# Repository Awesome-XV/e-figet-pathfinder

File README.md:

# e-figet-pathfinder
This is a project that allows you to play around with switches and LED's. It's a reaction game ... for now, I am planning to make a settings/page button that allows you to play different game modes and stuff. But now it's geared toward an *F1* style gameplay where the LED's close in on the center light and then they all go blank and it measures the time for you to let go of the "clutch" and hit the "accelerator". Maybe different racing types later??
I made this project as an intro into PCB's, circuits and soldering because it's my first physical project that I have done. I wanted to get into the hardware project and there was a nice guide, but no soldering guide so I get to do that on my own. So this is a bit later, and I added a battery compartment to it, it's now a mobile device and it doesn't have to be plugged in. I also am now planning to add a GT practice shifter to the code where you can practice shifting GT style. I also had to add 2 connectors so that I can solder the battery wires correctly.

# Some Pics

# BOM Table
| Name | Purpose | Quantity | Total Cost (USD) | Distributor | Link |
|------|---------|:--------:|-----------------:|-------------|------|
| XIAO RP2040 | MC, controls everything | 1 | $4.68 | Digikey | [Buy](https://www.digikey.com/en/products/detail/seeed-technology-co-ltd/102010428/14672129) |
| LED RED 5MM | Lights up | 7 | $1.05 | Digikey | [Buy](https://www.digikey.com/en/products/detail/w%C3%BCrth-elektronik/151051RS11000/4490012) |
| Through Hole Resistors | For the LEDs | 10 | $0.22 | Digikey | [Buy](https://www.digikey.com/en/products/detail/stackpole-electronics-inc/CF18JT110R/1741570) |
| MX SWITCH 12V | Switch to trigger actions | 4 | $5.00 | Digikey | [Buy](https://www.digikey.com/en/products/detail/cherry-americas-llc/MX1A-C1NW/280855) |
| BLACK KEYCAPS | Keycaps for the MX switches | 1 | $5.95 | Digikey | [Buy](https://www.digikey.com/en/products/detail/adafruit-industries-llc/4997/14552180) |
| Battery Compartment | To hold the batteries | 1 | $1.77 | Digikey | [Buy](https://www.digikey.com/en/products/detail/keystone-electronics/2465/303814) |
| Connectors | To provide a place for the red and black wires to hook onto | 10 | $0.29 | Digikey | [Buy](https://www.digikey.com/en/products/detail/adam-tech/PH1-01-UA/9830231) |
| Diode | To prevent reverse current flow | 1 | $0.18 | Digikey | [Buy](https://www.digikey.com/en/products/detail/smc-diode-solutions/1N5817/21705460) |
| PCB | For connection | 1 | $2.00 | JLCPCB | N/A |
| Shipping | Move these parts | 1 | $10.29 | JLCPCB, Digikey | N/A |
| Tax | I have to pay | 1 | $2.22 | Digikey | N/A |
| Tariffs | Quantity means 5 products I have tax on | 5 | $0.79 | Digikey | N/A |
| **Total** | | | *$34.44* | | |

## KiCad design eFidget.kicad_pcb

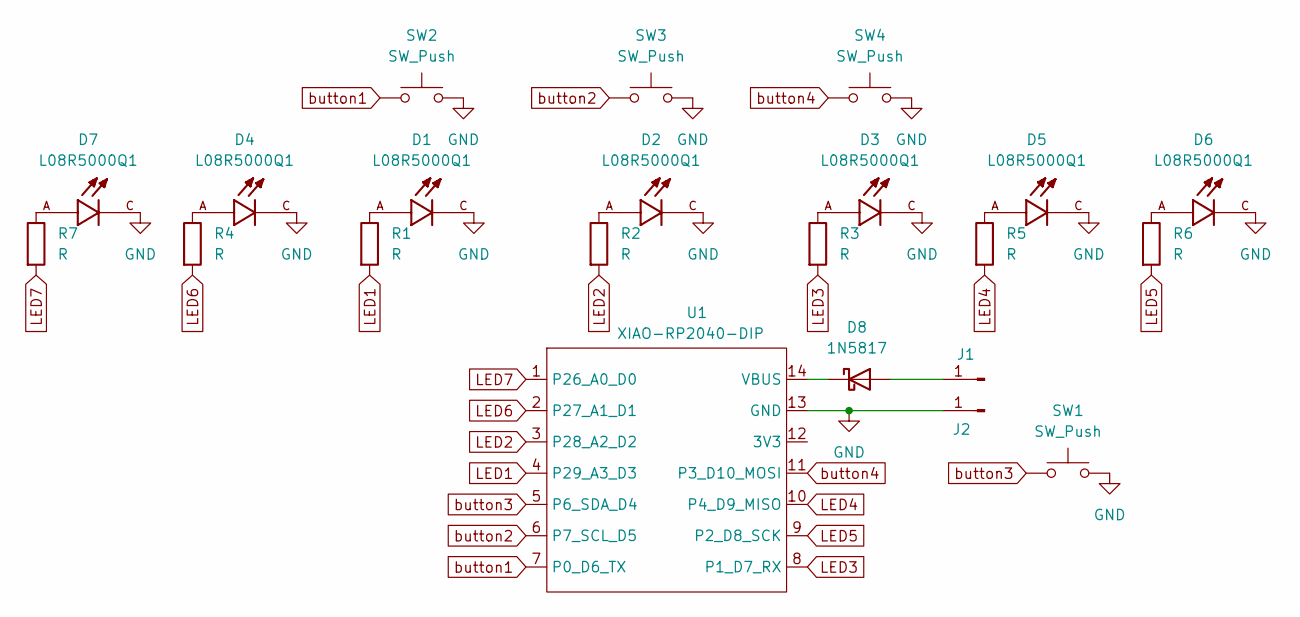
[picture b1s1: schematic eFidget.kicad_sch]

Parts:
D1, D2, D3, D4, D5, D6, D7: L08R5000Q1; LEDRD254W57D500H1070; PARTREV NA
D8: 1N5817; D_DO-41_SOD81_P10.16mm_Horizontal
J1, J2: Conn_01x01_Pin; PinHeader_1x01_P2.54mm_Vertical
R1, R2, R3, R4, R5, R6, R7: R; R_Axial_DIN0204_L3.6mm_D1.6mm_P5.08mm_Horizontal
SW1, SW2, SW3, SW4: SW_Push; SW_Cherry_MX_1.00u_PCB
U1: XIAO-RP2040-DIP

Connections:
GND: D1.C, D2.C, D3.C, D4.C, D5.C, D6.C, D7.C, J2.1, SW1.2, SW2.2, SW3.2, SW4.2, U1.13 (GND)
LED1: R1.2, U1.4 (P29_A3_D3)
LED2: R2.2, U1.3 (P28_A2_D2)
LED3: R3.2, U1.8 (P1_D7_RX)
LED4: R5.2, U1.10 (P4_D9_MISO)
LED5: R6.2, U1.9 (P2_D8_SCK)
LED6: R4.2, U1.2 (P27_A1_D1)
LED7: R7.2, U1.1 (P26_A0_D0)
unnamed: D1.A, R1.1
unnamed: D2.A, R2.1
unnamed: D3.A, R3.1
unnamed: D4.A, R4.1
unnamed: D5.A, R5.1
unnamed: D6.A, R6.1
unnamed: D7.A, R7.1
unnamed: D8.2 (A), J1.1
unnamed: D8.1 (K), U1.14 (VBUS)
button1: SW2.1, U1.7 (P0_D6_TX)
button2: SW3.1, U1.6 (P7_SCL_D5)
button3: SW1.1, U1.5 (P6_SDA_D4)
button4: SW4.1, U1.11 (P3_D10_MOSI)

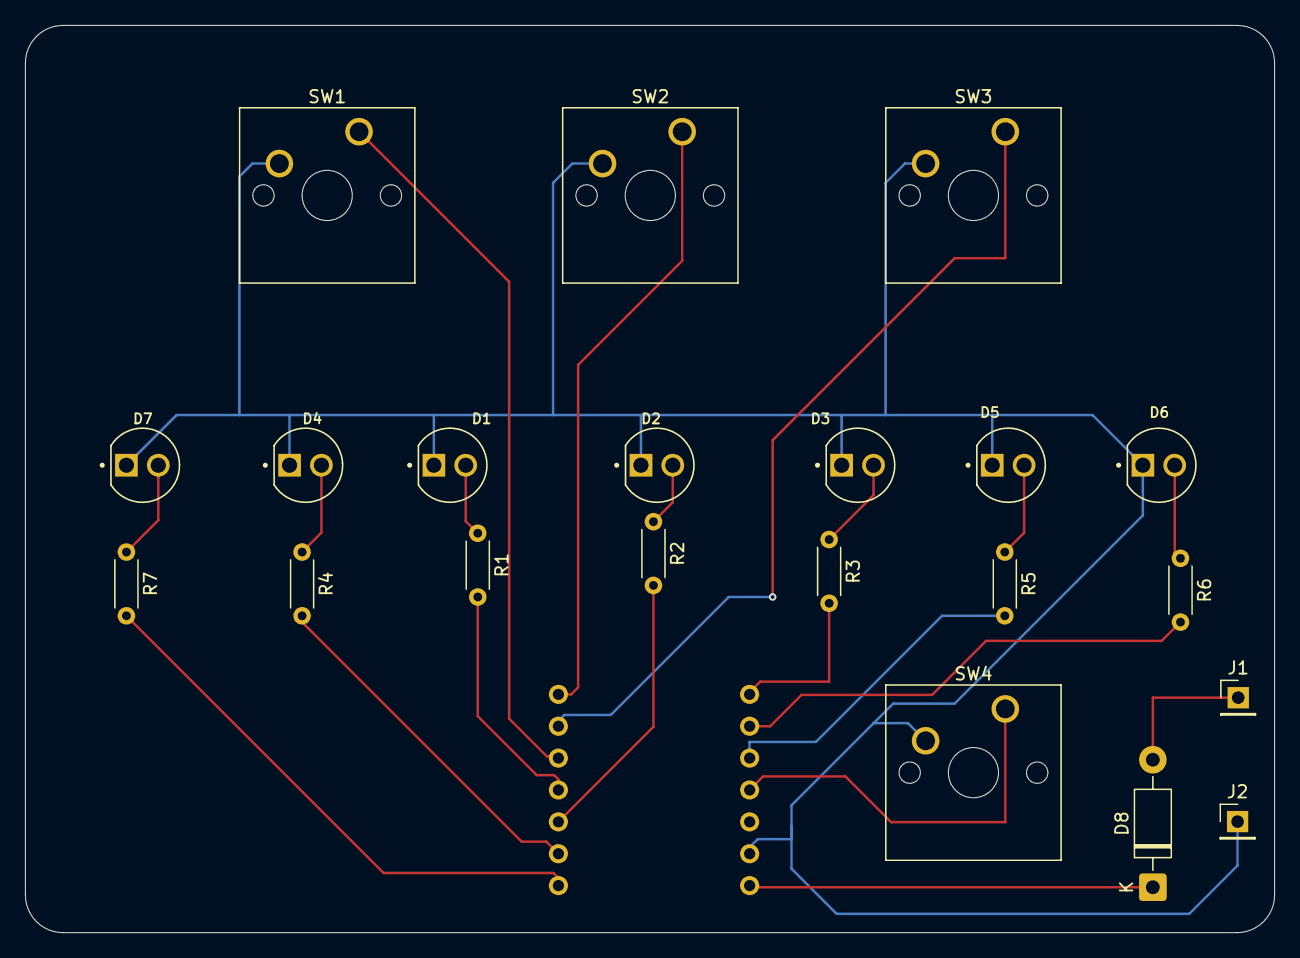
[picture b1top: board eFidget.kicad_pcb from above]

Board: 2 copper layers, 99.5 x 72.3 mm, 22 parts (1 on the bottom side), 21 nets.

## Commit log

2026-03-24 Adding KiCad Files
    All KiCad files used
2026-03-24 Add Prod Zip Files
    These are the files used to actually request the PCB
2026-03-25 Update README
    Include info about project and make the BOM available in the README.
2026-03-25 Add .STEP Files
2026-03-30 Add BOM
2026-03-30 Add step file
2026-03-30 Update BOM
2026-03-30 Add Arduino Firmware
2026-04-01 Update all files with new submission
2026-04-01 Update README
    Added new images and updated project description with additional details about battery compartment and connectors.
2026-04-01 Update step file
